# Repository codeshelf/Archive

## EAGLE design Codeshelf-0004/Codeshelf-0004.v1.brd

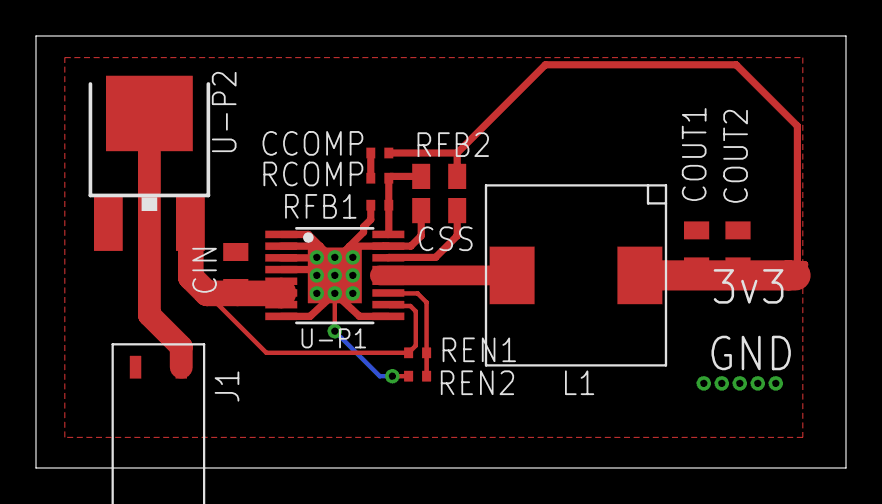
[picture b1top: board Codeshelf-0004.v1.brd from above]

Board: 2 copper layers, 45.0 x 24.0 mm, 14 parts (0 on the bottom side), 9 nets.

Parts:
CCOMP: 47pF; RF-C0402
CIN: 4.7uF; RF-C0805
COUT1, COUT2: 22uF; RF-C0805
CSS: 2.7nF; RF-C0805
J1: HEADER-2X-2.54MM; HEADER-2X-RA-2.54MM
L1: SLF10165
RCOMP: 13.7K; RF-R0402
REN1: 20K; RF-R0402
REN2: 10K; RF-R0402
RFB1: 76.8K; RF-R0402
RFB2: 240K; RF-C0805
U-P1: LM2854MH; HTSSOP16PWP
U-P2: PCHANNEL-MOSFET-DPAK; DPAK

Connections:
+3V3: CCOMP.2, COUT1.1, COUT2.1, L1.2, RFB2.2
GND: CIN.2, COUT1.2, COUT2.2, CSS.2, J1.2, REN2.1, RFB1.1, U-P1.1, U-P1.2, U-P1.3, U-P1.4, U-P1.8, U-P1.9, U-P1.15, U-P1.EXP, U-P2.1
unnamed: CSS.1, U-P1.14
unnamed: L1.1, U-P1.12, U-P1.13
unnamed: RCOMP.2, RFB1.2, RFB2.1, U-P1.16
unnamed: CCOMP.1, RCOMP.1
unnamed: REN1.1, REN2.2, U-P1.11
V-PROT: CIN.1, REN1.2, U-P1.5, U-P1.6, U-P1.7, U-P1.10, U-P2.3
VBATT: J1.1, U-P2.4

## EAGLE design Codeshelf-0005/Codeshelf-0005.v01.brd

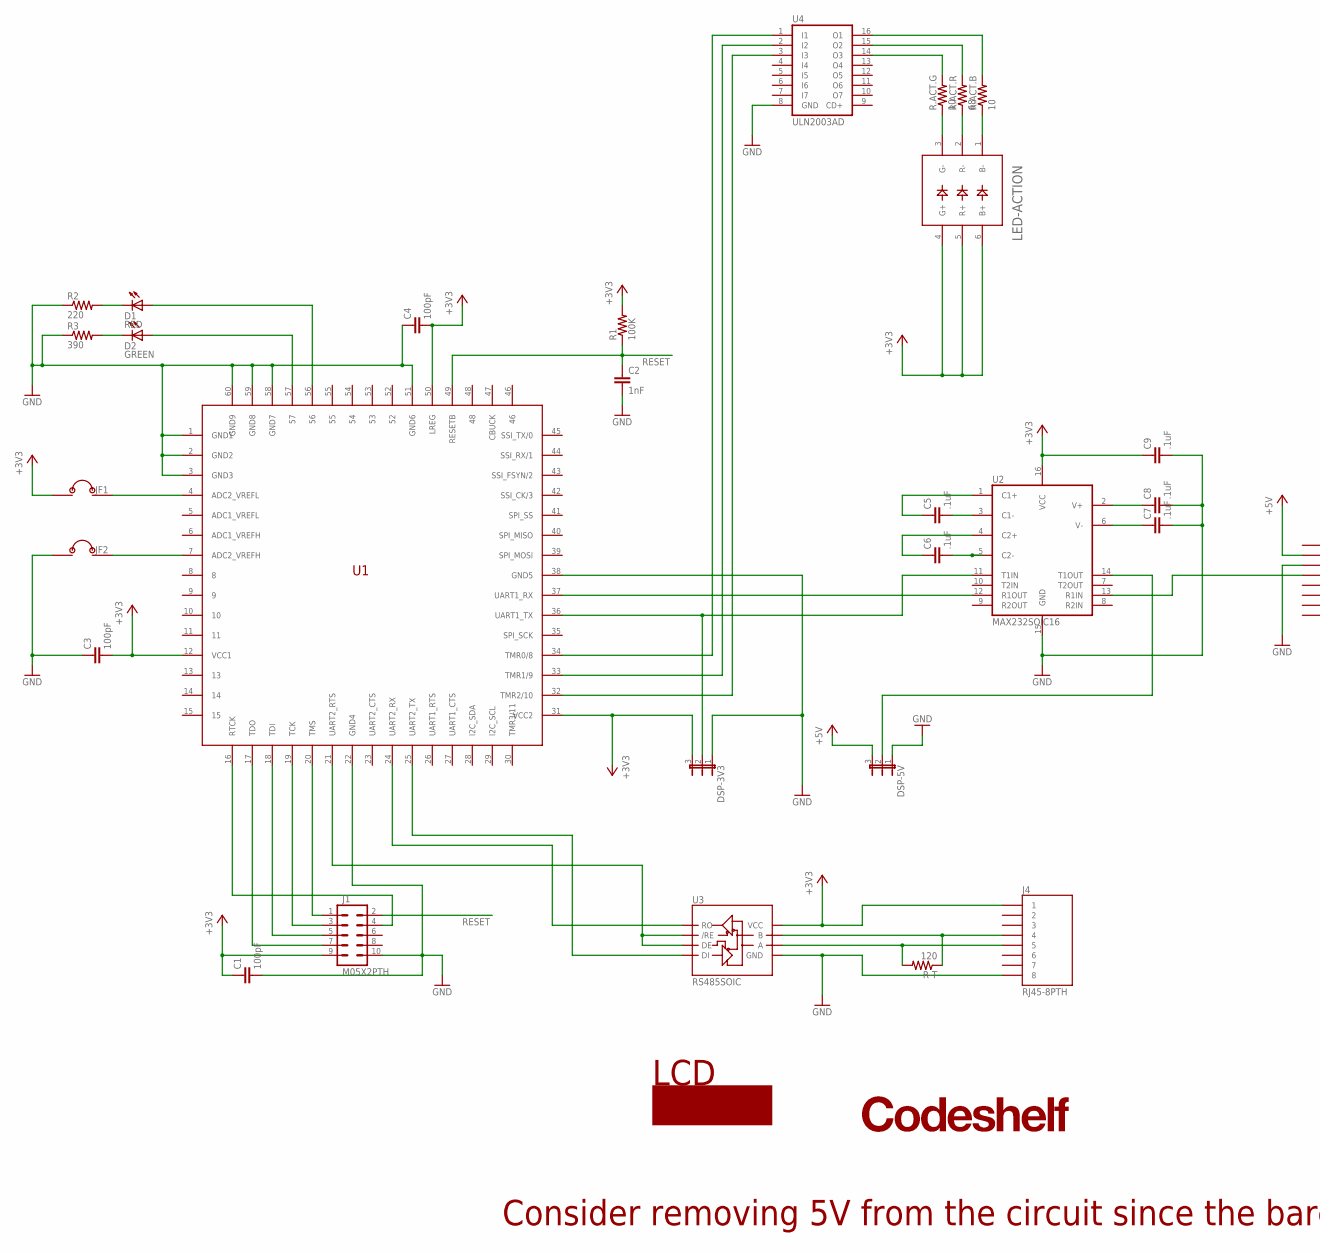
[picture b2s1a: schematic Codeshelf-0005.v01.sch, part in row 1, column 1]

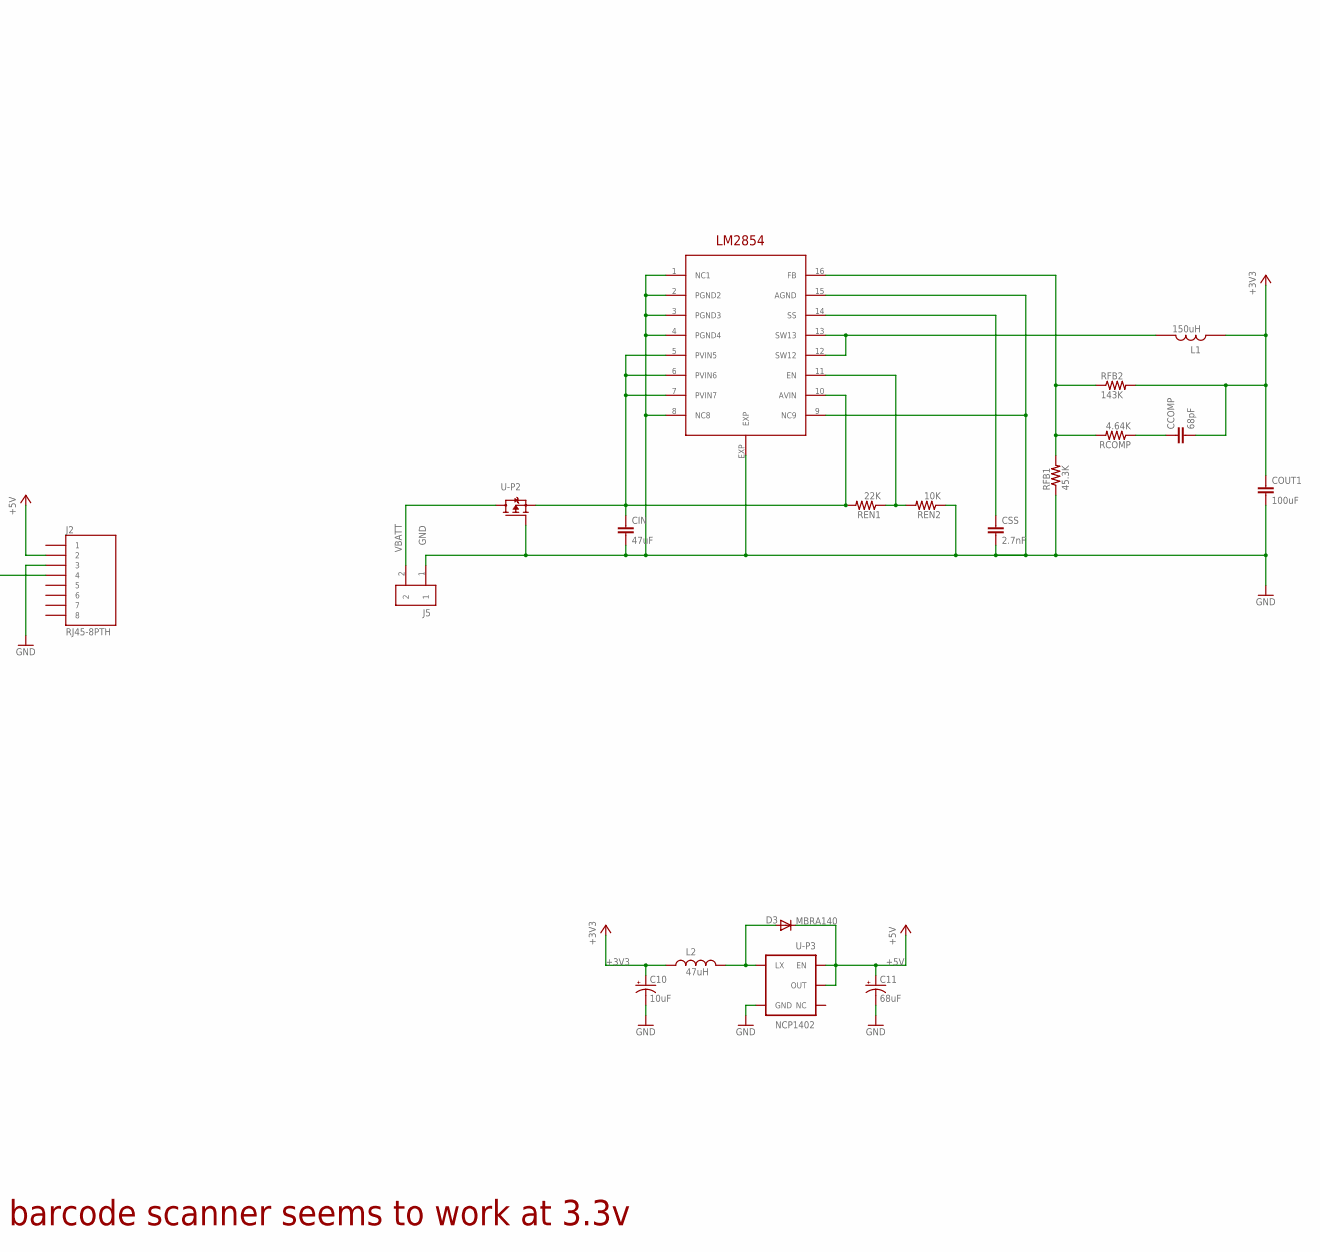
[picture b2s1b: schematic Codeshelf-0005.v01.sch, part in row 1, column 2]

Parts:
C1, C3, C4: 100pF; C0603
C2: 1nF; C0603
C5, C6, C7, C8, C9: .1uF; C0402
C10: 10uF; EIA3216
C11: 68uF; EIA3528
CCOMP: 68pF; C0805
CIN: 47uF; C1210K
COUT1: 100uF; C1210K
CSS: 2.7nF; C0805
D1: RED; CHIP-LED0805
D2: GREEN; CHIP-LED0805
D3: MBRA140; SMA-DIODE
DSP-3V3, DSP-5V: JUMPER-3PTH; 1X03
J1: M05X2PTH; AVR_ICSP
J2, J4: RJ45-8PTH; RJ45-8
J5: HEADER-2X-2.54MM; HEADER-2X-RA-2.54MM
JF1, JF2: JUMPER-2X-SMT-VIA; JUMPER-VIA-2X
L1: 150uH; SLF10165
L2: 47uH; CR54
LCD: LCD-SPARKFUN; LCD-20X4-SPARKFUN
LED-ACTION: LED5060A; PLCC-6
LOGO: CODESHELF-LOGO
R1: 100K; RF-R0402
R2: 220; RF-R0402
R3: 390; RF-R0402
R-T: 120; RF-R0402
R.ACT.B, R.ACT.G: 10; RF-R0402
R.ACT.R: 68; RF-R0402
RCOMP: 4.64K; RF-R0402
REN1: 22K; RF-R0402
REN2: 10K; RF-R0402
RFB1: 45.3K; RF-R0402
RFB2: 143K; RF-R0402
U1: ZSFM201-1A; ZSFM201-1
U2: MAX232SOIC16; SO016
U3: RS485SOIC; SO08
U4: ULN2003AD; SO16
U-P1: LM2854MH; HTSSOP16PWP
U-P2: PCHANNEL-MOSFET-DPAK; DPAK
U-P3: NCP1402; SOT23-5

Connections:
+3V3: C1.1, C3.2, C4.2, C9.1, C10.A (+), CCOMP.2, COUT1.1, DSP-3V3.3, J1.9, J4.1, JF1.1, L1.2, L2.P$1 (1), LED-ACTION.4 (G+), LED-ACTION.5 (R+), LED-ACTION.6 (B+), R1.2, RFB2.2, U1.12 (VCC1), U1.31 (VCC2), U1.50 (LREG), U2.16 (VCC), U3.8 (VCC)
+5V: C11.A (+), D3.C, DSP-5V.3, J2.2, U-P3.1 (EN), U-P3.2 (OUT)
C1: C5.1, U2.1 (C1+)
C2: C6.1, U2.4 (C2+)
GND: C1.2, C2.2, C3.1, C4.1, C7.2, C8.2, C9.2, C10.C (-), C11.C (-), CIN.2, COUT1.2, CSS.2, DSP-3V3.1, DSP-5V.1, J1.10, J2.3, J4.8, J5.1, JF2.1, R2.1, R3.1, REN2.1, RFB1.1, U1.1 (GND1), U1.2 (GND2), U1.3 (GND3), U1.22 (GND4), U1.38 (GND5), U1.51 (GND6), U1.58 (GND7), U1.59 (GND8), U1.60 (GND9), U2.15 (GND), U3.5 (GND), U4.8 (GND), U-P1.1 (NC1), U-P1.2 (PGND2), U-P1.3 (PGND3), U-P1.4 (PGND4), U-P1.8 (NC8), U-P1.9 (NC9), U-P1.15 (AGND), U-P1.EXP, U-P2.1 (G), U-P3.4 (GND)
unnamed: D2.A, U1.57
unnamed: D1.A, U1.56
unnamed: D2.C, R3.2
unnamed: D1.C, R2.2
unnamed: D3.A, L2.P$2 (2), U-P3.5 (LX)
unnamed: JF2.2, U1.7 (ADC2_VREFH)
unnamed: JF1.2, U1.4 (ADC2_VREFL)
unnamed: C5.2, U2.3 (C1-)
unnamed: C6.2, U2.5 (C2-)
unnamed: C7.1, U2.6 (V-)
unnamed: C8.1, U2.2 (V+)
unnamed: U1.25 (UART2_TX), U3.4 (DI)
unnamed: U1.24 (UART2_RX), U3.1 (RO)
unnamed: U1.21 (UART2_RTS), U3.2 (/RE), U3.3 (DE)
unnamed: J4.4, R-T.1, U3.7 (B)
unnamed: J4.5, R-T.2, U3.6 (A)
unnamed: CSS.1, U-P1.14 (SS)
unnamed: L1.1, U-P1.12 (SW12), U-P1.13 (SW13)
unnamed: RCOMP.2, RFB1.2, RFB2.1, U-P1.16 (FB)
unnamed: CCOMP.1, RCOMP.1
unnamed: REN1.1, REN2.2, U-P1.11 (EN)
unnamed: R.ACT.R.2, U4.15 (O2)
unnamed: R.ACT.G.2, U4.14 (O3)
unnamed: LED-ACTION.1 (B-), R.ACT.B.1
unnamed: LED-ACTION.2 (R-), R.ACT.R.1
unnamed: LED-ACTION.3 (G-), R.ACT.G.1
unnamed: U1.34 (TMR0/8), U4.1 (I1)
unnamed: U1.33 (TMR1/9), U4.2 (I2)
unnamed: R.ACT.B.2, U4.16 (O1)
unnamed: U1.32 (TMR2/10), U4.3 (I3)
R1IN: J2.4, U2.13 (R1IN)
R1OUT: U1.37 (UART1_RX), U2.12 (R1OUT)
RESET: C2.1, J1.2, R1.1, U1.49 (RESETB)
RTCK: J1.4, U1.16 (RTCK)
T1IN: DSP-3V3.2, U1.36 (UART1_TX), U2.11 (T1IN)
T1OUT: DSP-5V.2, U2.14 (T1OUT)
TCK: J1.3, U1.19 (TCK)
TDI: J1.5, U1.18 (TDI)
TDO: J1.7, U1.17 (TDO)
TMS: J1.1, U1.20 (TMS)
V-PROT: CIN.1, REN1.2, U-P1.5 (PVIN5), U-P1.6 (PVIN6), U-P1.7 (PVIN7), U-P1.10 (AVIN), U-P2.3 (S)
VBATT: J5.2, U-P2.4 (D)

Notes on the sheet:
Consider removing 5V from the circuit since the barcode scanner seems to work at 3.3v

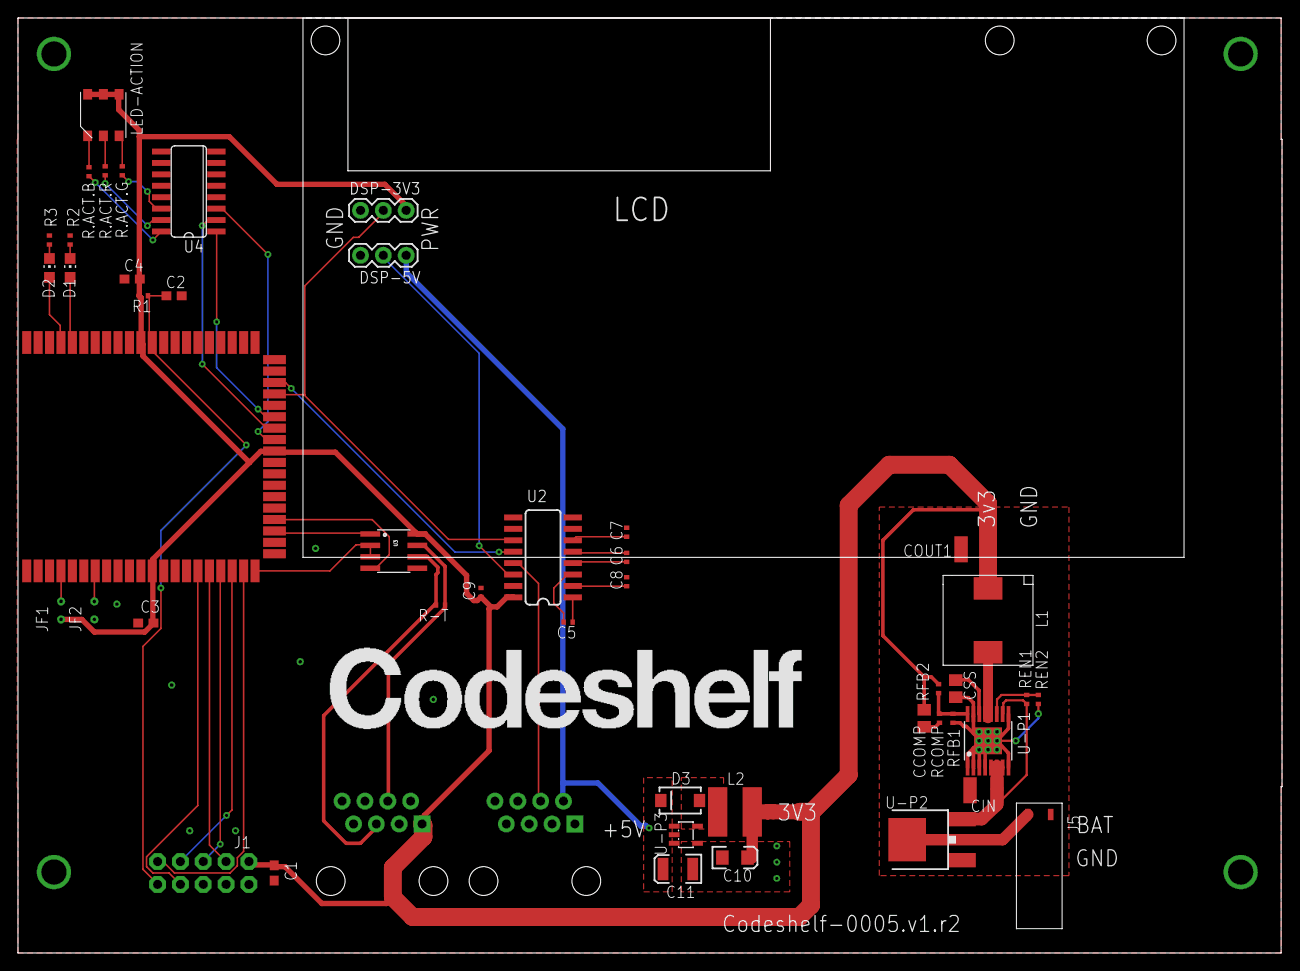
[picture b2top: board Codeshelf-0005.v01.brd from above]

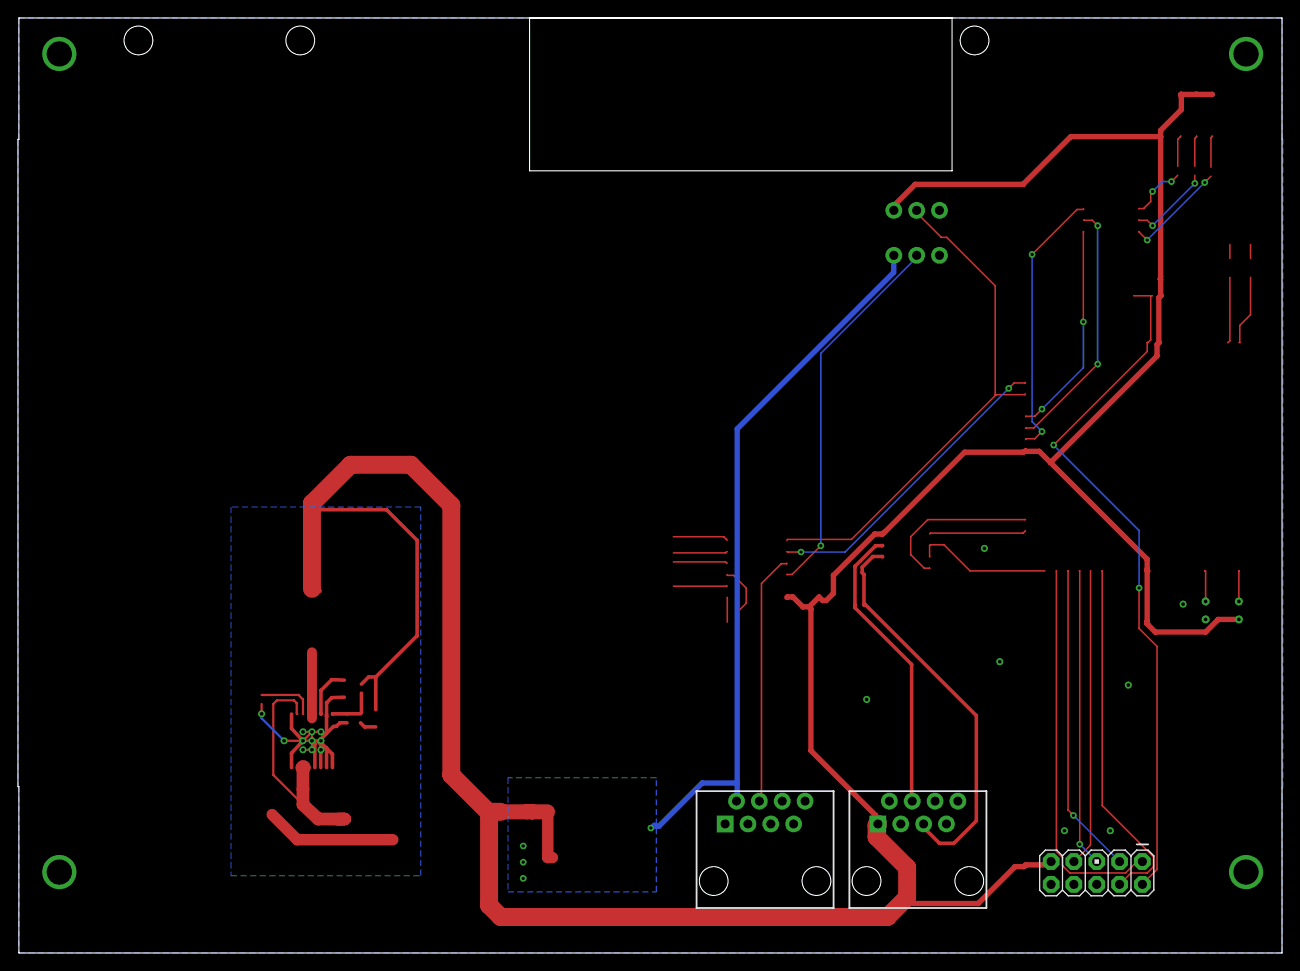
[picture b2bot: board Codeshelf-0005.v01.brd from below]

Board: 2 copper layers, 140.6 x 104.0 mm, 50 parts (3 on the bottom side), 47 nets.

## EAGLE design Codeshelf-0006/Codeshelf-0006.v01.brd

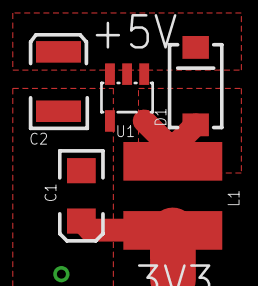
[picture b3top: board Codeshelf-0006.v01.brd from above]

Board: 2 copper layers, 5 parts (0 on the bottom side), 4 nets.

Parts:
C1: 10uF; EIA3216
C2: 68uF; EIA3528
D1: MBRA140; SMA-DIODE
L1: 47uH; CR54
U1: NCP1402; SOT23-5

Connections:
+3V3: C1.A, L1.P$1
+5V: C2.A, D1.C, U1.1, U1.2
GND: C1.C, C2.C, U1.4
unnamed: D1.A, L1.P$2, U1.5

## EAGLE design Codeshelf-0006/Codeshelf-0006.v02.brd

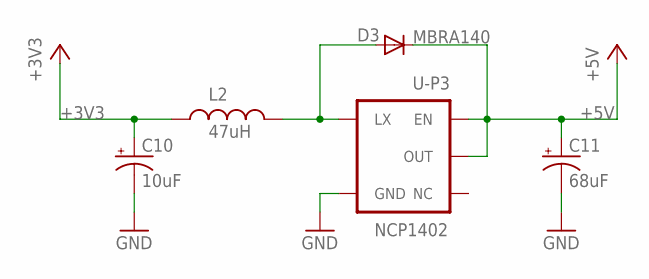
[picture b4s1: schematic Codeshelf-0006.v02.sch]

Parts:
C10: 10uF; EIA3216
C11: 68uF; EIA3528
D3: MBRA140; SMA-DIODE
L2: 47uH; CR54
U-P3: NCP1402; SOT23-5

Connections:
+3V3: C10.A (+), L2.P$1 (1)
+5V: C11.A (+), D3.C, U-P3.1 (EN), U-P3.2 (OUT)
GND: C10.C (-), C11.C (-), U-P3.4 (GND)
unnamed: D3.A, L2.P$2 (2), U-P3.5 (LX)

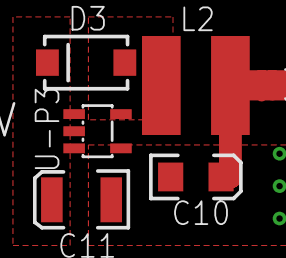
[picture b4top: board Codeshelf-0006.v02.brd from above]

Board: 2 copper layers, 5 parts (0 on the bottom side), 4 nets.

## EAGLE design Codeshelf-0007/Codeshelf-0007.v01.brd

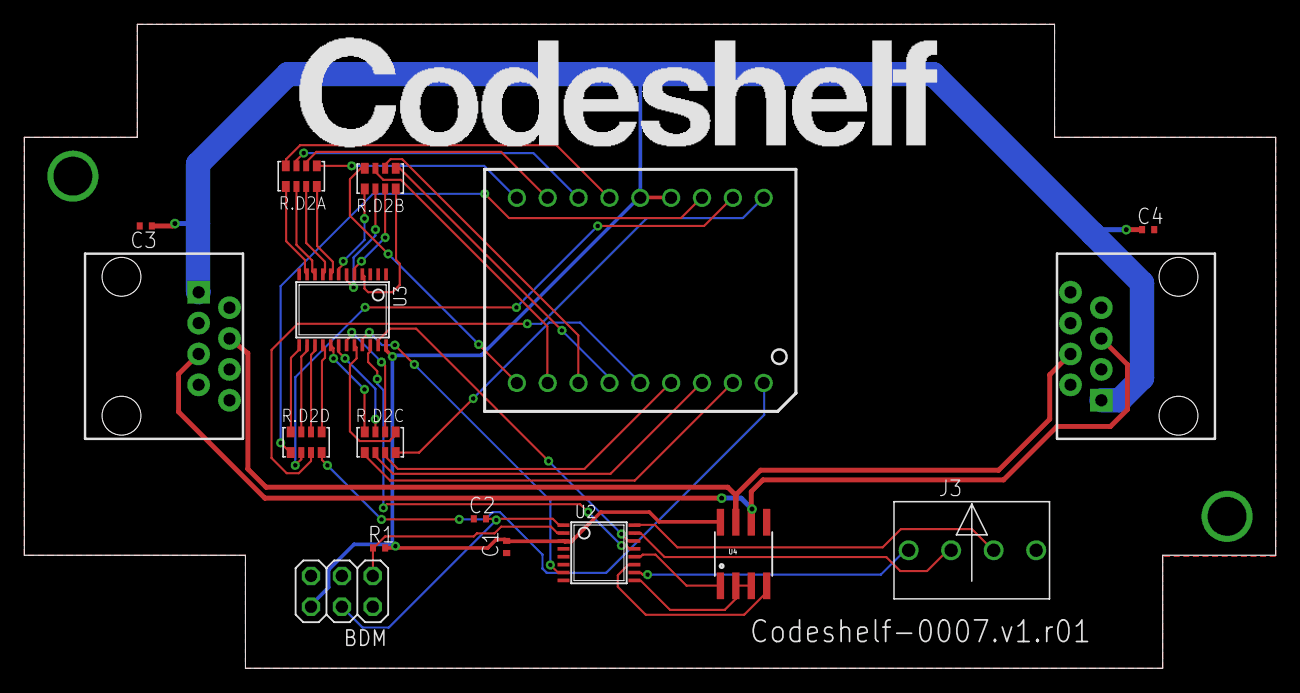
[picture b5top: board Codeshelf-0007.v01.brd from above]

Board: 2 copper layers, 103.0 x 53.0 mm, 18 parts (0 on the bottom side), 47 nets.

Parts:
BDM: HEADER-3X2
C1, C2, C3, C4: .1uF; RF-C0402
J1, J2: RJ45-8PTH; RJ45-8
J3: HEADER-4X39357; MOLEX-39357-0004
LOGO: CODESHELF-LOGO
R1: 3.3K; RF-R0402
R.D2A, R.D2B, R.D2C, R.D2D: RESISTOR-ARRAY-4X-3216; 3216-4X
U2: MC9S08QG-DT; TSSOP16
U3: CAT9552; TSSOP24
U4: RS485SOIC; SO08
U7: 7SEGMENT-2DIGIT; 7SEGMENT-2DIG-.54

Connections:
+3V3: BDM.6, C1.1, C3.1, C4.1, J1.1, J2.1, R1.2, U2.3, U3.24, U4.8, U7.13, U7.14
A: J1.5, J2.5, U4.6
B: J1.4, J2.4, U4.7
GND: BDM.2, C1.2, C2.1, C3.2, J1.8, J2.8, J3.4, U2.4, U3.1, U3.2, U3.3, U3.12, U4.5
unnamed: J3.3, U2.16
unnamed: J3.2, U2.15
unnamed: J3.1, U2.10
unnamed: BDM.1, R1.1, U2.2
unnamed: R.D2D.8, U3.13
unnamed: R.D2D.7, U3.14
unnamed: R.D2D.6, U3.15
unnamed: R.D2D.5, U3.16
unnamed: R.D2C.8, U3.17
unnamed: R.D2C.7, U3.18
unnamed: R.D2C.6, U3.19
unnamed: R.D2C.5, U3.20
unnamed: U2.9, U4.2, U4.3
unnamed: BDM.4, C2.2, U2.1
unnamed: R.D2A.5, U3.11
unnamed: R.D2A.6, U3.10
unnamed: R.D2A.7, U3.9
unnamed: R.D2A.1, U7.18
unnamed: R.D2A.2, U7.17
unnamed: R.D2A.8, U3.8
unnamed: R.D2B.5, U3.7
unnamed: R.D2B.6, U3.6
unnamed: R.D2B.7, U3.5
unnamed: R.D2B.8, U3.4
unnamed: R.D2A.3, U7.16
unnamed: R.D2A.4, U7.15
unnamed: R.D2B.4, U7.1
unnamed: R.D2B.3, U7.2
unnamed: R.D2B.2, U7.3
unnamed: R.D2B.1, U7.4
unnamed: R.D2D.1, U7.12
unnamed: R.D2D.2, U7.11
unnamed: R.D2D.3, U7.10
unnamed: R.D2D.4, U7.9
unnamed: R.D2C.1, U7.8
unnamed: R.D2C.2, U7.7
unnamed: R.D2C.3, U7.6
unnamed: R.D2C.4, U7.5
RESET: U2.7, U3.21
RX: U2.12, U4.1
SLA: U2.14, U3.23
SLC: U2.13, U3.22
TX: U2.11, U4.4

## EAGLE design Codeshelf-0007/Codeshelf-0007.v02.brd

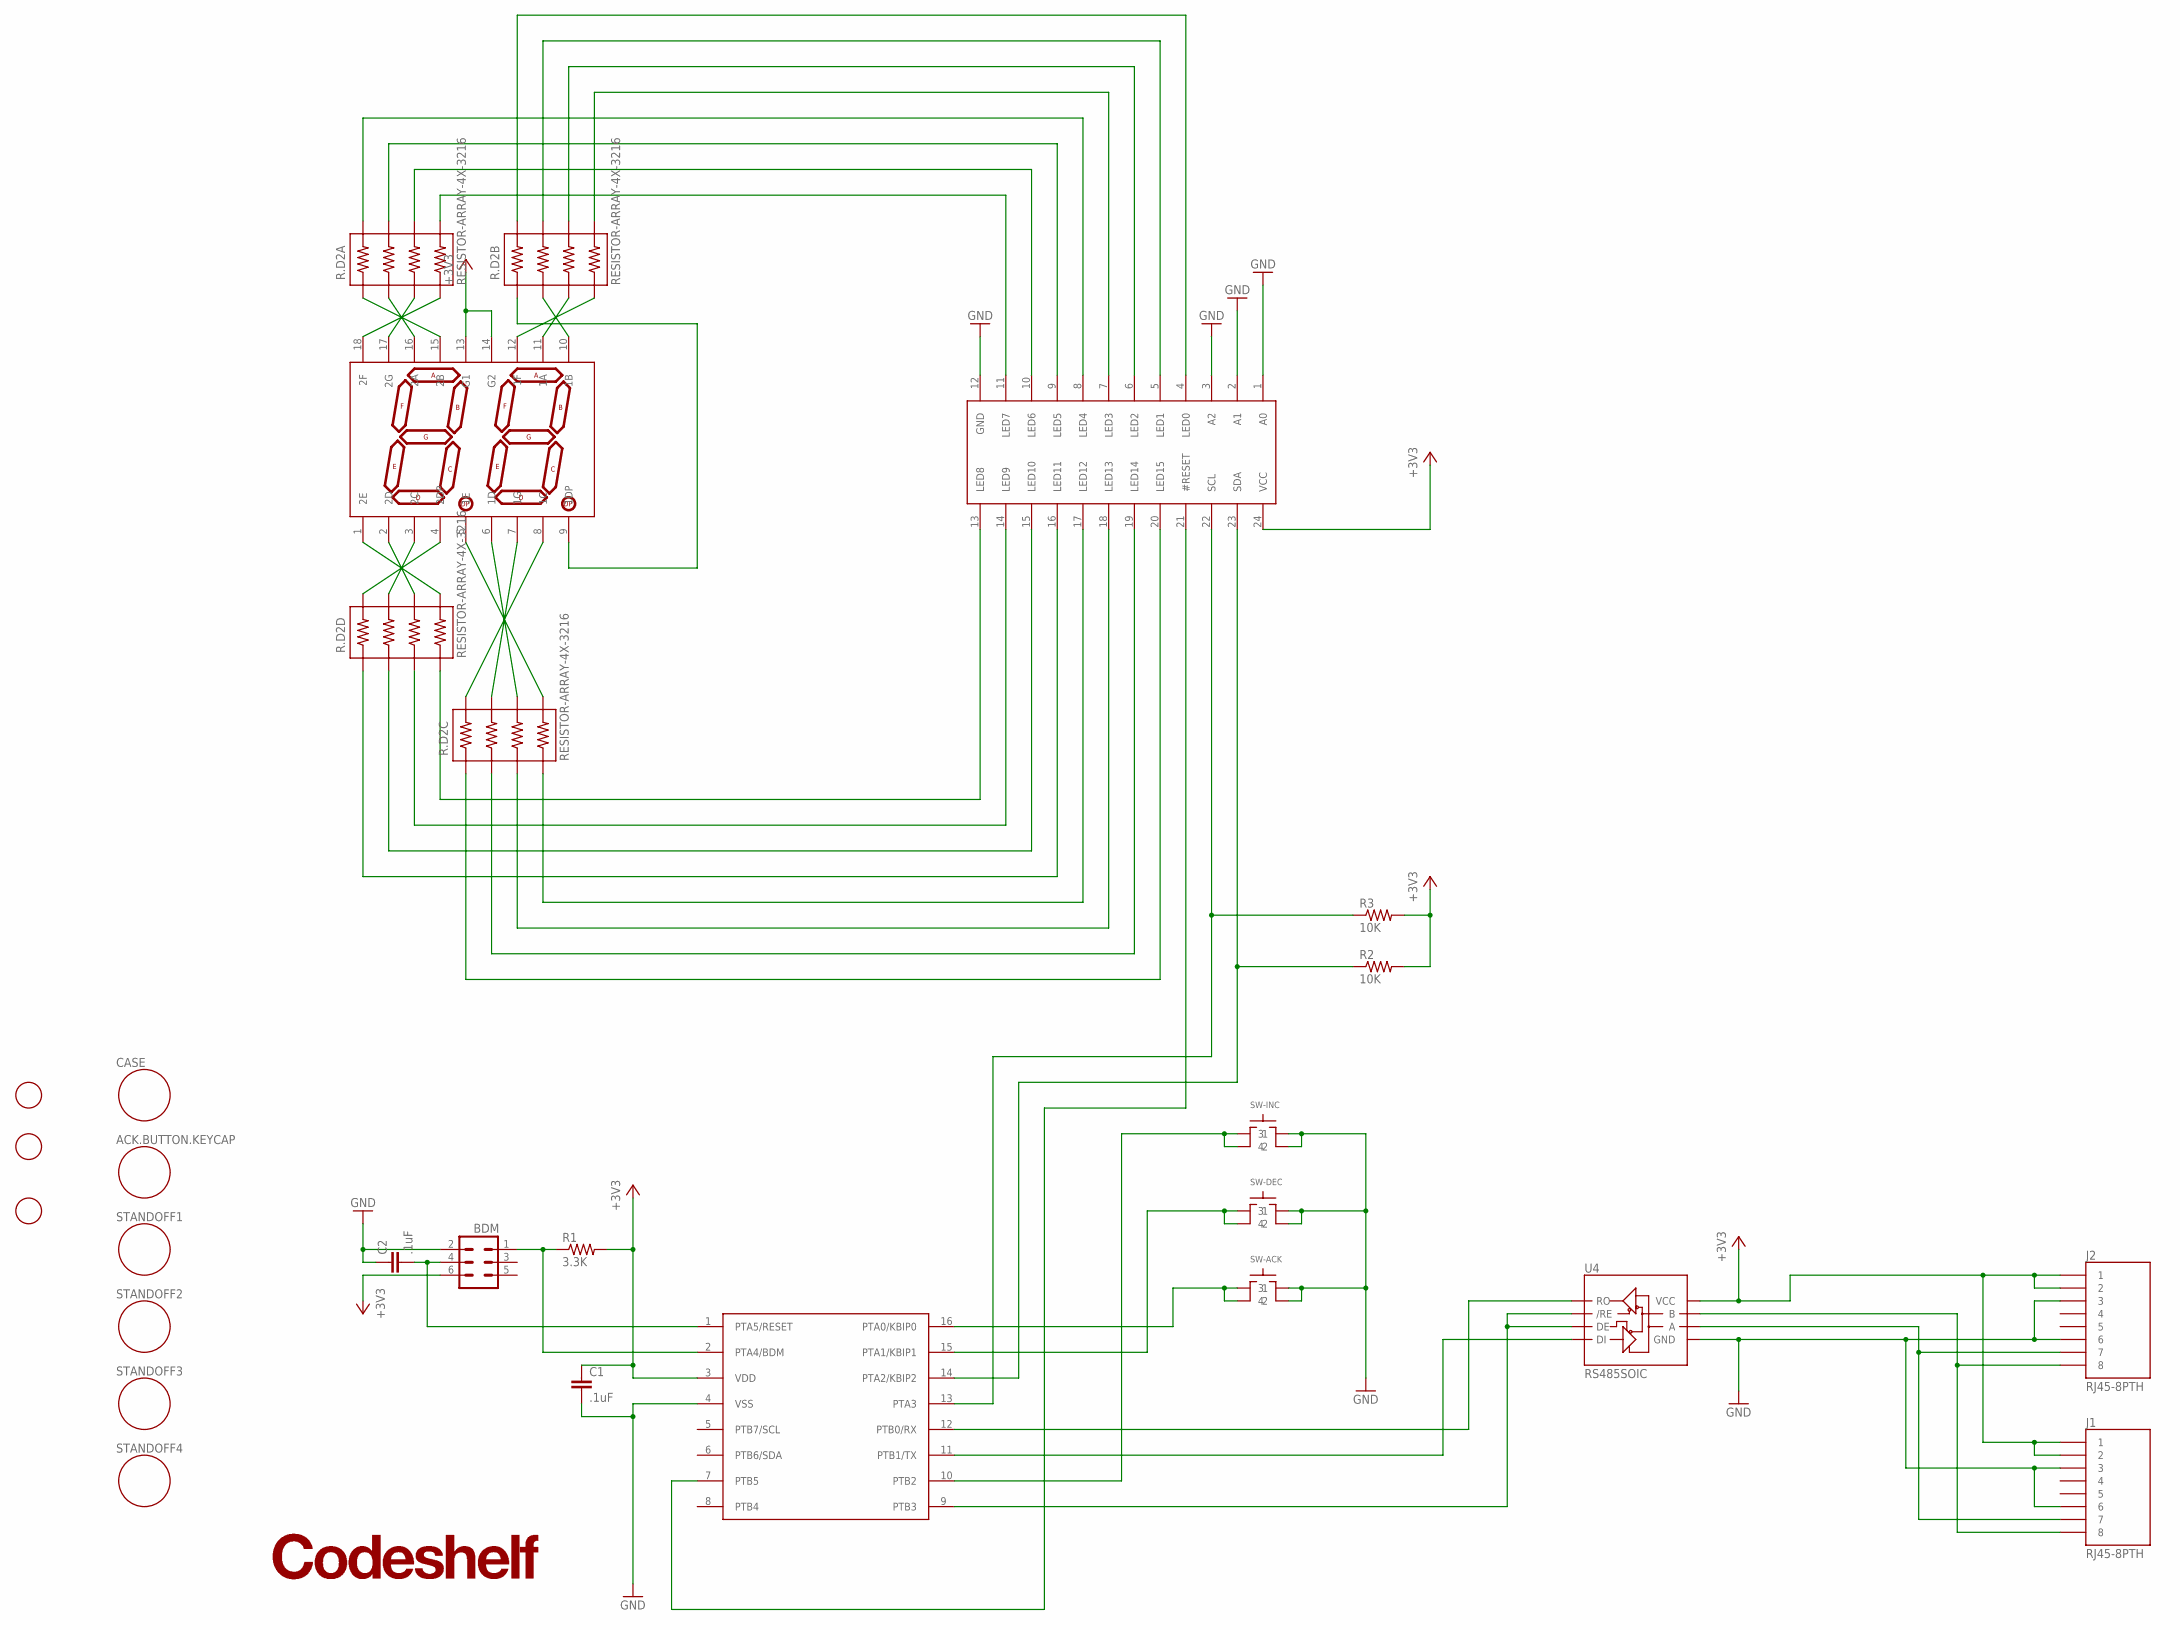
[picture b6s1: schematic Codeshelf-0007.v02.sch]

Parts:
ACK.BUTTON.KEYCAP: EXTERNAL-COMPONENT
BDM: HEADER-3X2
C1, C2: .1uF; C0402
CASE: EXTERNAL-COMPONENT; MFGP PN-1321-C
J1, J2: RJ45-8PTH; RJ45-8
LOGO: CODESHELF-LOGO
R1: 3.3K; RF-R0402
R2, R3: 10K; RF-R0402
R.D2A, R.D2B, R.D2C, R.D2D: RESISTOR-ARRAY-4X-3216; 3216-4X
STANDOFF1, STANDOFF2, STANDOFF3, STANDOFF4: EXTERNAL-COMPONENT
SW-ACK: SWITCH-TACTILE-320.03E11
SW-DEC: SWITCH-TACTILE-FSM
SW-INC: SWITCH-TACTILE-FSM
U2: MC9S08QG-DT; TSSOP16
U3: CAT9552; TSSOP24
U4: RS485SOIC; SO08
U7: 7SEGMENT-2DIGIT; 7SEGMENT-2DIG-.54
U$1, U$2, U$3: FIDUCIAL; FIDUCIAL_1MM

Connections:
+3V3: BDM.6, C1.1, J1.1, J1.2, J2.1, J2.2, R1.2, R2.2, R3.2, U2.3 (VDD), U3.24 (VCC), U4.8 (VCC), U7.13 (G1), U7.14 (G2)
GND: BDM.2, C1.2, C2.1, J1.3, J1.6, J2.3, J2.6, SW-ACK.P$3 (3), SW-ACK.P$4 (4), SW-DEC.P$3 (3), SW-DEC.P$4 (4), SW-INC.P$3 (3), SW-INC.P$4 (4), U2.4 (VSS), U3.1 (A0), U3.2 (A1), U3.3 (A2), U3.12 (GND), U4.5 (GND)
unnamed: R.D2A.5 (4B), U3.11 (LED7)
unnamed: R.D2A.6 (3B), U3.10 (LED6)
unnamed: R.D2A.7 (2B), U3.9 (LED5)
unnamed: R.D2A.8 (1B), U3.8 (LED4)
unnamed: R.D2B.5 (4B), U3.7 (LED3)
unnamed: SW-ACK.P$1 (1), SW-ACK.P$2 (2), U2.16 (PTA0/KBIP0)
unnamed: SW-DEC.P$1 (1), SW-DEC.P$2 (2), U2.15 (PTA1/KBIP1)
unnamed: SW-INC.P$1 (1), SW-INC.P$2 (2), U2.10 (PTB2)
unnamed: BDM.1, R1.1, U2.2 (PTA4/BDM)
unnamed: R.D2B.6 (3B), U3.6 (LED2)
unnamed: R.D2B.7 (2B), U3.5 (LED1)
unnamed: R.D2B.8 (1B), U3.4 (LED0)
unnamed: R.D2D.8 (1B), U7.4 (2DP)
unnamed: R.D2D.7 (2B), U7.3 (2C)
unnamed: R.D2D.6 (3B), U7.2 (2D)
unnamed: R.D2D.5 (4B), U7.1 (2E)
unnamed: R.D2A.1 (1A), U7.15 (2B)
unnamed: R.D2A.2 (2A), U7.16 (2A)
unnamed: U2.9 (PTB3), U4.2 (/RE), U4.3 (DE)
unnamed: R.D2A.3 (3A), U7.17 (2G)
unnamed: R.D2A.4 (4A), U7.18 (2F)
unnamed: R.D2B.4 (4A), U7.12 (1F)
unnamed: BDM.4, C2.2, U2.1 (PTA5/RESET)
unnamed: R.D2B.3 (3A), U7.11 (1A)
unnamed: R.D2C.8 (1B), U7.8 (1C)
unnamed: R.D2C.7 (2B), U7.7 (1G)
unnamed: R.D2C.6 (3B), U7.6 (1D)
unnamed: R.D2C.5 (4B), U7.5 (1E)
unnamed: R.D2B.1 (1A), U7.9 (1DP)
unnamed: R.D2B.2 (2A), U7.10 (1B)
unnamed: R.D2D.4 (4A), U3.13 (LED8)
unnamed: R.D2D.3 (3A), U3.14 (LED9)
unnamed: R.D2D.2 (2A), U3.15 (LED10)
unnamed: R.D2D.1 (1A), U3.16 (LED11)
unnamed: R.D2C.4 (4A), U3.17 (LED12)
unnamed: R.D2C.3 (3A), U3.18 (LED13)
unnamed: R.D2C.2 (2A), U3.19 (LED14)
unnamed: R.D2C.1 (1A), U3.20 (LED15)
RESET: U2.7 (PTB5), U3.21 (#RESET)
RS485_N: J1.8, J2.8, U4.7 (B)
RS485_P: J1.7, J2.7, U4.6 (A)
RX: U2.12 (PTB0/RX), U4.1 (RO)
SLA: R2.1, U2.14 (PTA2/KBIP2), U3.23 (SDA)
SLC: R3.1, U2.13 (PTA3), U3.22 (SCL)
TX: U2.11 (PTB1/TX), U4.4 (DI)

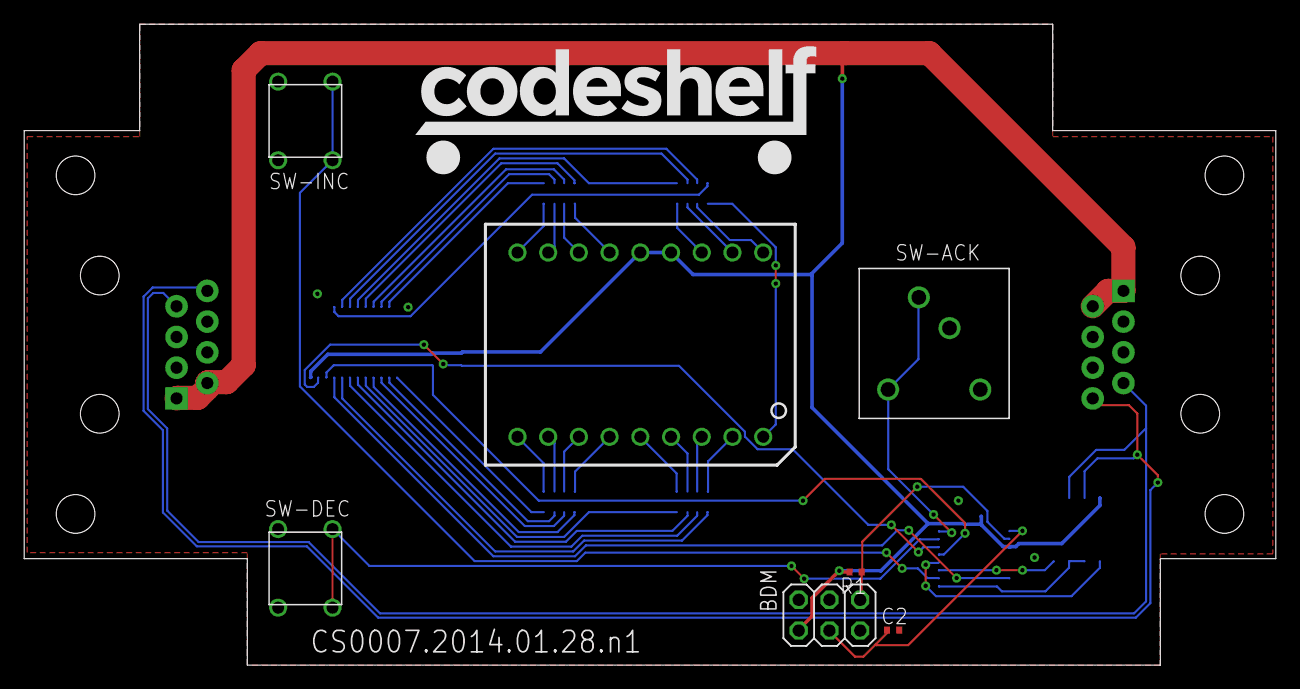
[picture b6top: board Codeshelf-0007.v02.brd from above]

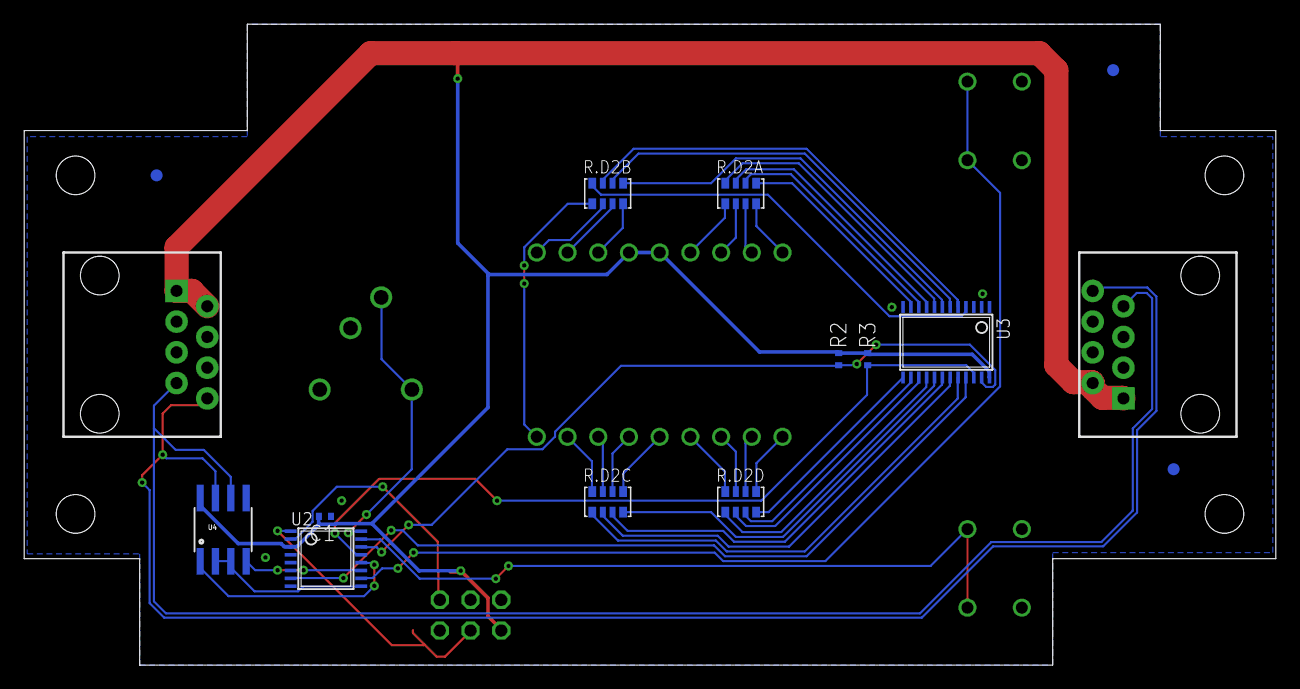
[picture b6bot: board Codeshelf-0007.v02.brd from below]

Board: 2 copper layers, 103.5 x 53.0 mm, 29 parts (15 on the bottom side), 47 nets.
